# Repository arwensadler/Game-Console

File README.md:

# Game-Console

Check out the demo video here: https://vimeo.com/492182079

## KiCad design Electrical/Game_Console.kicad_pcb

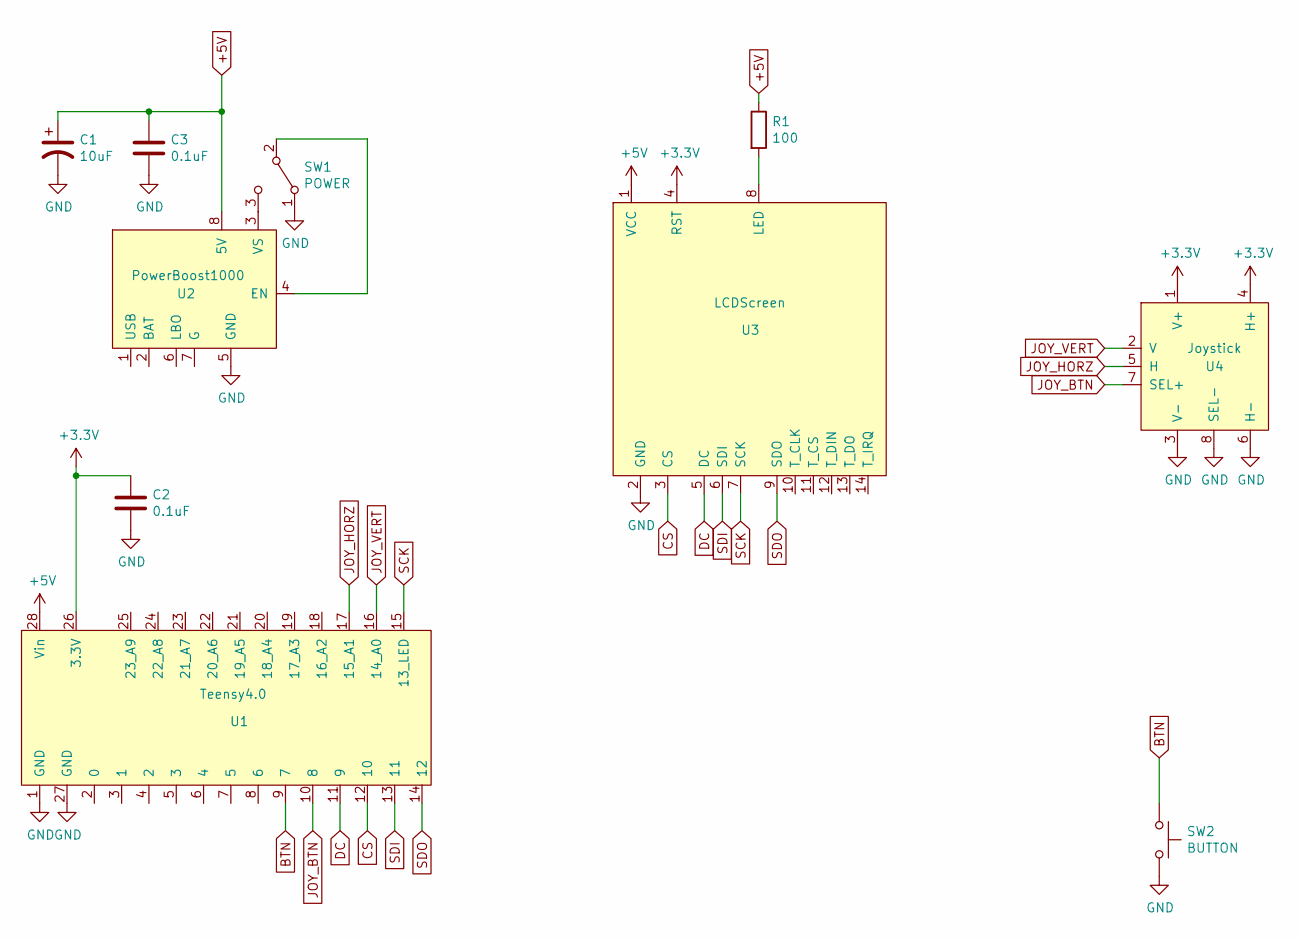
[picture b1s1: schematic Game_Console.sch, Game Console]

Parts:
C1: 10uF; CP_Radial_D5.0mm_P2.00mm
C2, C3: 0.1uF; C_Disc_D6.0mm_W4.4mm_P5.00mm
R1: 100; R_Through_Hole_eighth_watt
SW1: POWER; SPDT
SW2: BUTTON; SW_PUSH_6mm_H4.3mm
U1: Teensy4.0; Teensy
U2: PowerBoost1000; Power_Boost
U3: LCDScreen; LCD Screen
U4: Joystick

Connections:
+3V3: C2.1, U1.26 (3.3V), U3.4 (RST), U4.1 (V+), U4.4 (H+)
+5V: C1.1, C3.1, R1.1, U1.28 (Vin), U2.8 (5V), U3.1 (VCC)
BTN: SW2.1, U1.9 (7)
DC: U1.11 (9), U3.5 (DC)
GND: C1.2, C2.2, C3.2, SW1.1 (A), SW2.2, U1.1 (GND), U1.27 (GND), U2.5 (GND), U3.2 (GND), U4.3 (V-), U4.6 (H-), U4.8 (SEL-)
I2C_SCK: U1.15 (13_LED), U3.7 (SCK)
JOY_BTN: U1.10 (8), U4.7 (SEL+)
JOY_HORZ: U1.17 (15_A1), U4.5 (H)
JOY_VERT: U1.16 (14_A0), U4.2 (V)
LCD_CS: U1.12 (10), U3.3 (CS)
unnamed: R1.2, U3.8 (LED)
unnamed: SW1.2 (B), U2.4 (EN)
unnamed: SW1.3 (C), U2.3 (VS)
SDI: U1.13 (11), U3.6 (SDI)
SPI_SDO: U1.14 (12), U3.9 (SDO)

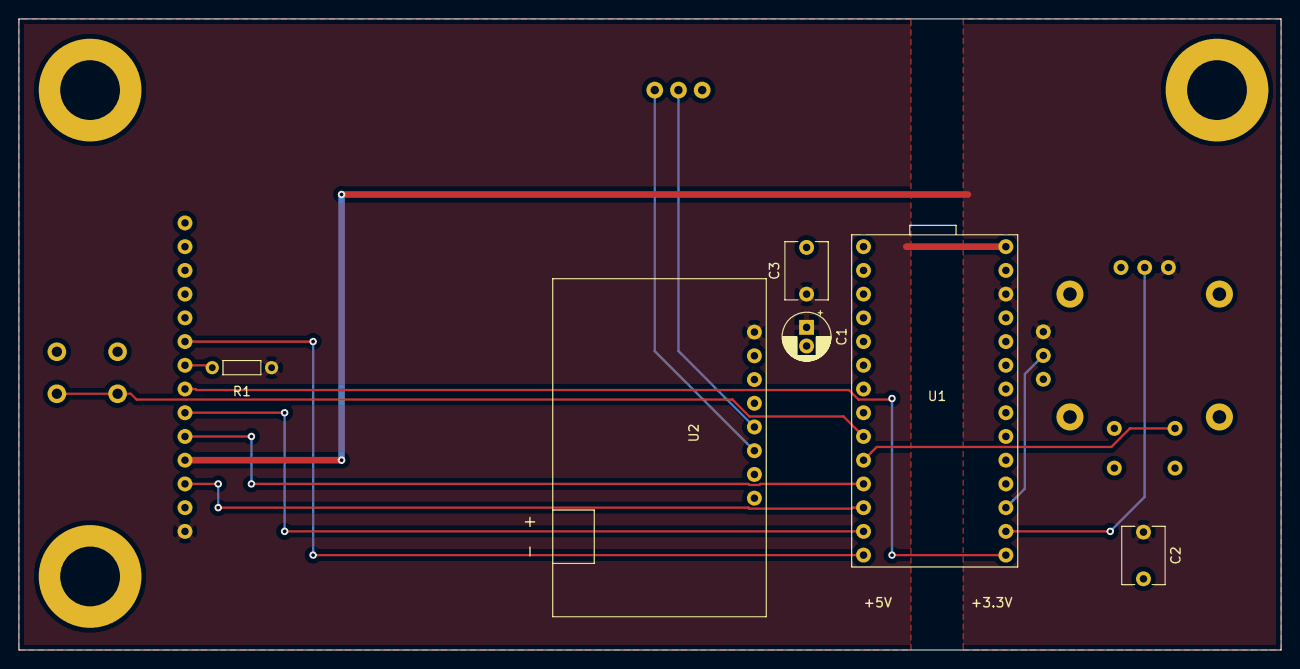
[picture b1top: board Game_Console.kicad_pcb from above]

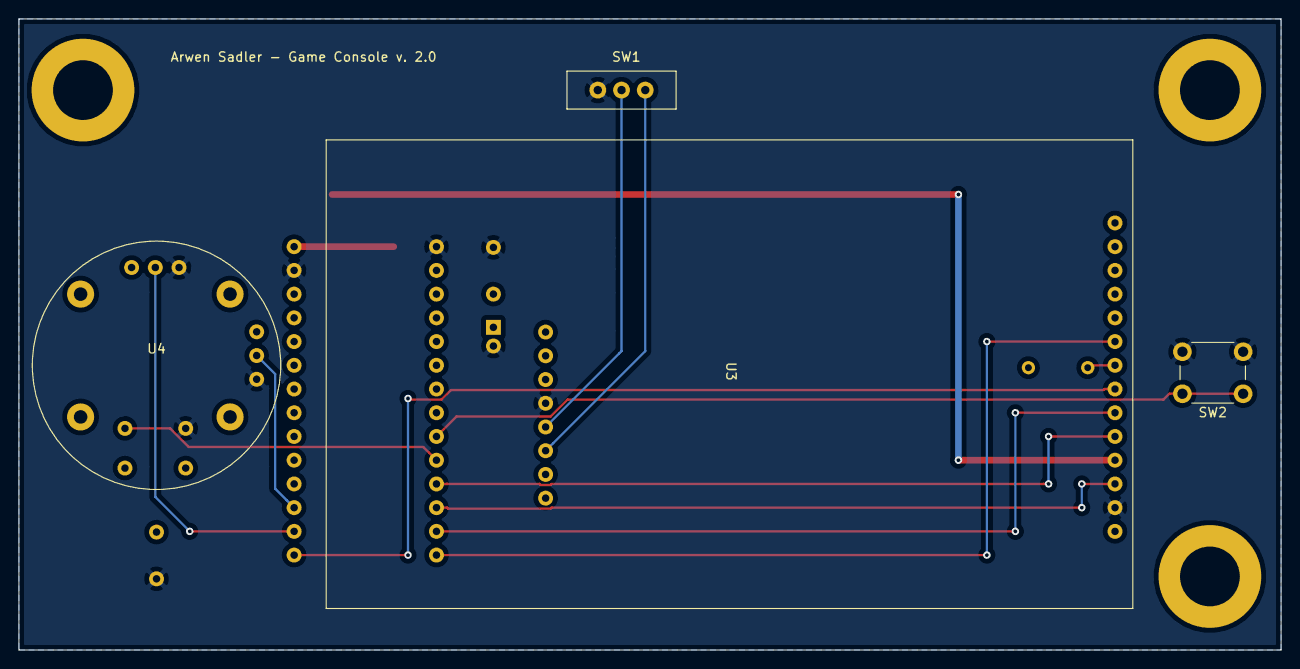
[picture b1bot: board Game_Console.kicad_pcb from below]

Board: 2 copper layers, 135.1 x 67.6 mm, 10 parts (4 on the bottom side), 15 nets.

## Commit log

2020-12-16 Add mechanical and electrical
2020-12-17 Add software
2020-12-17 Fix orientation and start delay
2020-12-17 Add demo video link
2020-12-17 Update schematic
